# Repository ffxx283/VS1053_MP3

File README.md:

# VS1053_MP3
基于VS1053芯片设计的MP3播放器

产品定位为一款可以对VS1053进行全面开发的开发板，产品的功能应当全面覆盖芯片的所有外设资源，但应该以将VS1053作为主控为重点，适当开发从机功能（SPI控制）。
TYPE-C接口，插入电脑直接对开发板进行下载调试（板载下载器），将读写SD卡的功能也加入此接口中（读卡器功能），可以使用跳线帽进行选择USB的通路。
带有液晶显示屏或者是OLED显示屏，带有按键，方便进行交互。

TYPE-C接口，插入电脑直接对开发板进行下载调试（板载下载器），将读写SD卡的功能也加入此接口中（读卡器功能），可以使用跳线帽进行选择USB的通路。

带有液晶显示屏或者是OLED显示屏，带有按键，方便进行交互。

主控：VS1053
USB转串口芯片：CH340N
SPI存储器芯片：AT93C66
电源芯片：RT9193-33GB、RT9193-18GB
SD卡控制器芯片：GL823
模拟单刀双掷开关SGM3157YC6/TR
显示屏选型：鸿欣达----YT144S025不带触摸
存储设备：TF卡
音频输入输出：3.5mm耳机孔输出+板载MIC

……
不测试了，下载调试软件的时候，软件直接就崩溃了，多次测试均未见效果，当成一个读卡器来用吧
VS1053芯片的生态不行，目前市面上大部分都是把它当做一个从机芯片来用，用作主机的案例太少，
官方对于此方面不够重视，软件也存在各种各样的问题，折腾不下去了。

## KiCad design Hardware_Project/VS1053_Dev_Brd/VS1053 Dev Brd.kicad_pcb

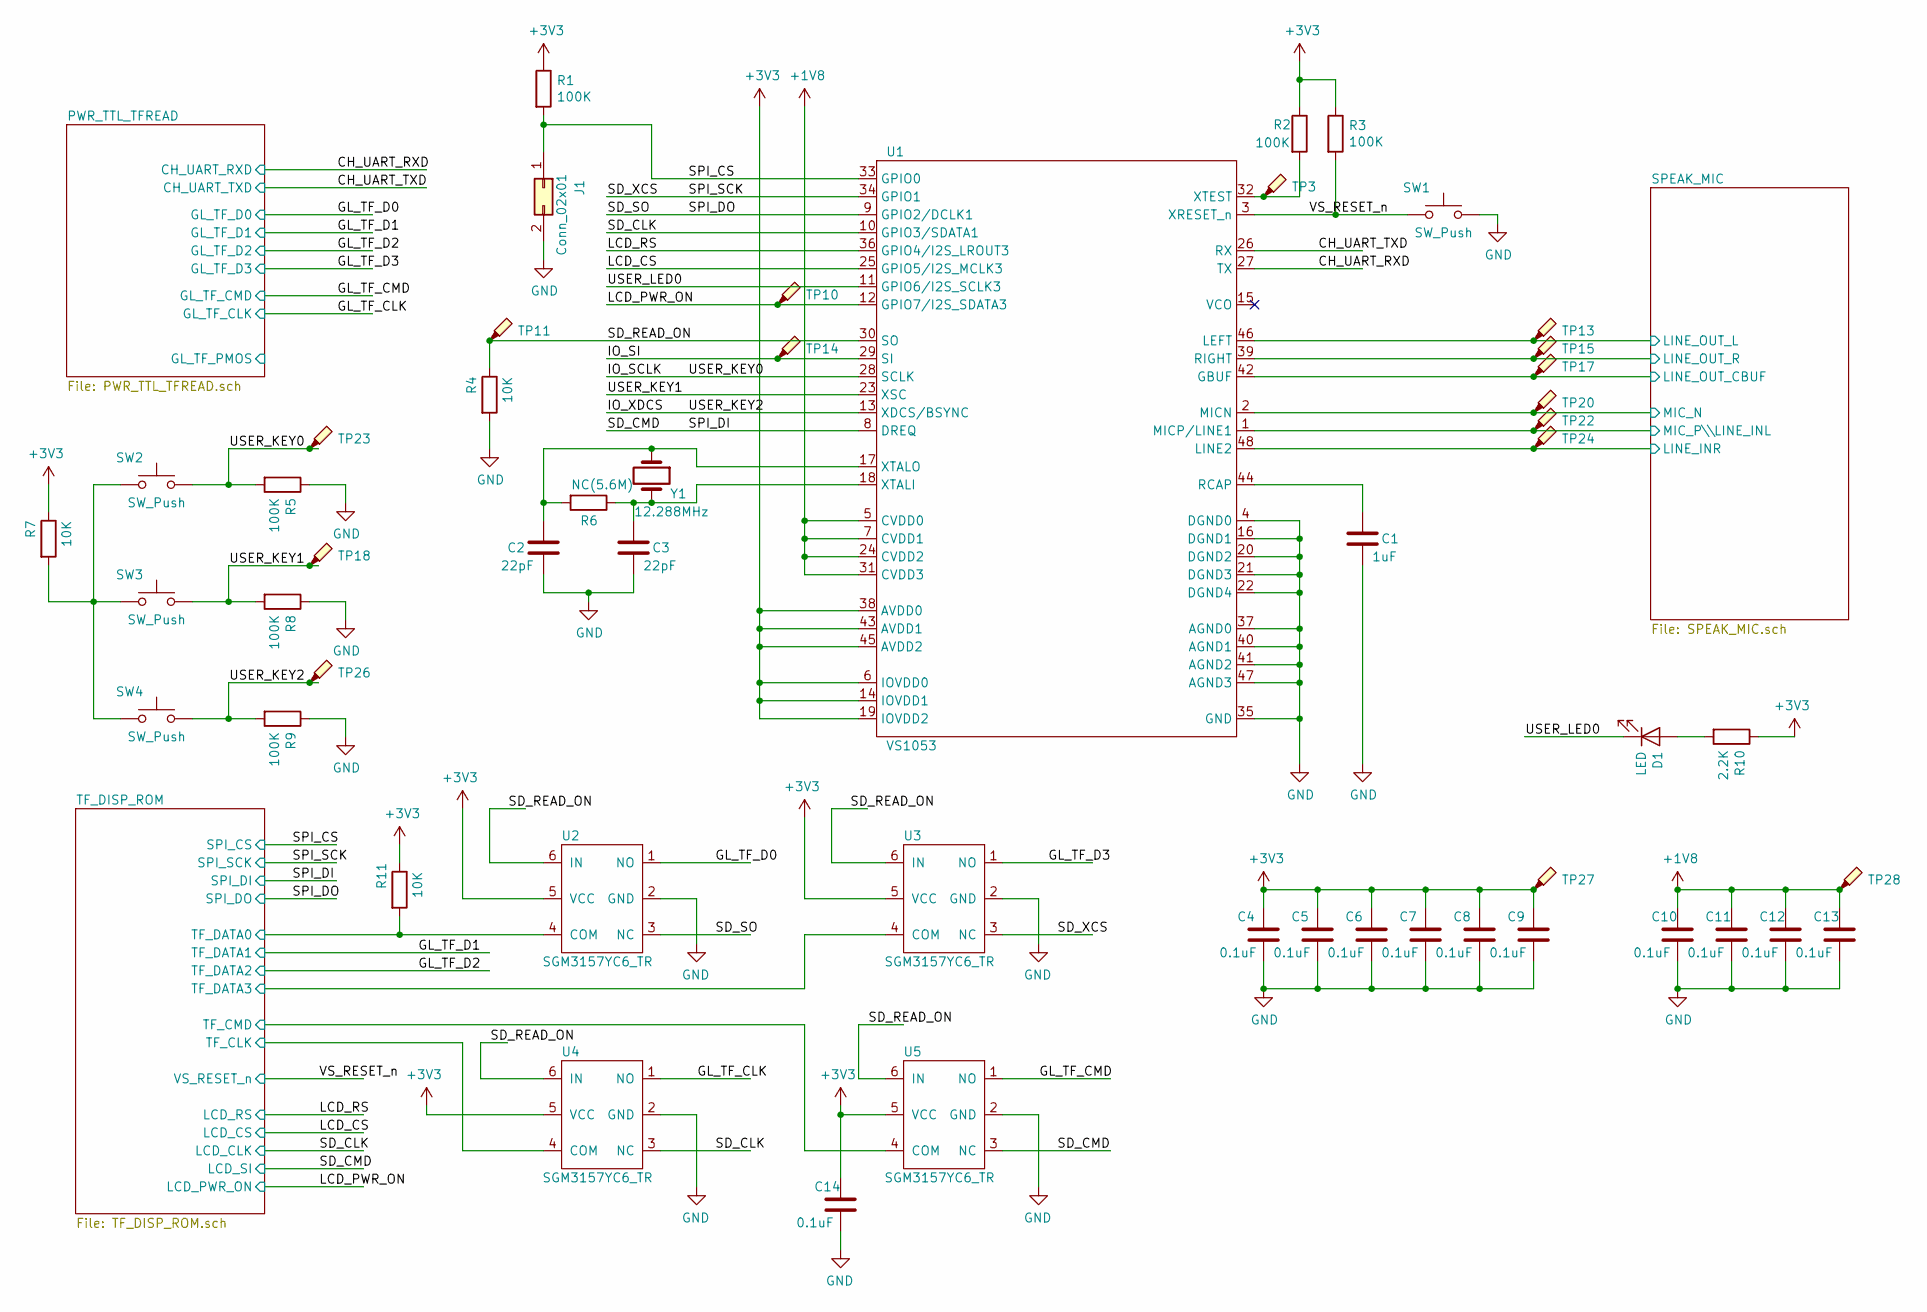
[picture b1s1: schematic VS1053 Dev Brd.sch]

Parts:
C1: 1uF; C_0603_1608Metric
C2, C3: 22pF; C_0402_1005Metric
C4, C5, C6, C7, C8, C9, C10, C11, C12, C13, C14: 0.1uF; C_0402_1005Metric
D1: LED; D_0603_1608Metric
J1: Conn_02x01; PinHeader_1x02_P2.00mm_Vertical
R1, R2, R3, R5, R8, R9: 100K; R_0402_1005Metric
R4, R7, R11: 10K; R_0402_1005Metric
R6: NC(5.6M); R_0402_1005Metric
R10: 2.2K; R_0402_1005Metric
SW1, SW2, SW3, SW4: SW_Push; SW_SPST_B3U-1000P
TP3, TP10, TP11, TP13, TP14, TP15, TP17, TP18, TP20, TP22, TP23, TP24, TP26, TP27, TP28: TestPoint_Probe; TestPoint_Pad_D1.0mm
U1: VS1053; LQFP-48_7x7mm_P0.5mm
U2, U3, U4, U5: SGM3157YC6_TR; SOT-363_SC-70-6
Y1: 12.288MHz; Crystal_HC49-4H_Vertical

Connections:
+1V8: C10.1, C11.1, C12.1, C13.1, TP28.1, U1.5 (CVDD0), U1.7 (CVDD1), U1.24 (CVDD2), U1.31 (CVDD3); also elsewhere on the board
+3V3: C4.1, C5.1, C6.1, C7.1, C8.1, C9.1, C14.1, R1.1, R2.1, R3.1, R7.1, R10.1, R11.1, TP27.1, U1.6 (IOVDD0), U1.14 (IOVDD1), U1.19 (IOVDD2), U1.38 (AVDD0), U1.43 (AVDD1), U1.45 (AVDD2), U2.5 (VCC), U3.5 (VCC), U4.5 (VCC), U5.5 (VCC); also elsewhere on the board
/CH_UART_RXD: U1.27 (TX); also elsewhere on the board
/CH_UART_TXD: U1.26 (RX); also elsewhere on the board
/GL_TF_CLK: U4.1 (NO); also elsewhere on the board
/GL_TF_CMD: U5.1 (NO); also elsewhere on the board
/GL_TF_D0: U2.1 (NO); also elsewhere on the board
/GL_TF_D3: U3.1 (NO); also elsewhere on the board
/IO_SCLK: R5.2, SW2.2, TP23.1, U1.28 (SCLK)
/IO_SI: TP14.1, U1.29 (SI)
/IO_XDCS: R9.2, SW4.2, TP26.1, U1.13 (XDCS/BSYNC)
/LCD_CS: U1.25 (GPIO5/I2S_MCLK3); also elsewhere on the board
/LCD_PWR_ON: TP10.1, U1.12 (GPIO7/I2S_SDATA3); also elsewhere on the board
/LCD_RS: U1.36 (GPIO4/I2S_LROUT3); also elsewhere on the board
/SD_CLK: U1.10 (GPIO3/SDATA1), U4.3 (NC); also elsewhere on the board
/SD_CMD: U1.8 (DREQ), U5.3 (NC); also elsewhere on the board
/SD_READ_ON: R4.1, TP11.1, U1.30 (SO), U2.6 (IN), U3.6 (IN), U4.6 (IN), U5.6 (IN)
/SD_SO: U1.9 (GPIO2/DCLK1), U2.3 (NC); also elsewhere on the board
/SD_XCS: U1.34 (GPIO1), U3.3 (NC); also elsewhere on the board
/SPEAK_MIC/LINE_INR: TP24.1, U1.48 (LINE2); also elsewhere on the board
/SPEAK_MIC/LINE_OUT_CBUF: TP17.1, U1.42 (GBUF); also elsewhere on the board
/SPEAK_MIC/LINE_OUT_L: TP13.1, U1.46 (LEFT); also elsewhere on the board
/SPEAK_MIC/LINE_OUT_R: TP15.1, U1.39 (RIGHT); also elsewhere on the board
/SPEAK_MIC/MIC_N: TP20.1, U1.2 (MICN); also elsewhere on the board
/SPEAK_MIC/MIC_P\LINE_INL: TP22.1, U1.1 (MICP/LINE1); also elsewhere on the board
/SPI_CS: J1.1, R1.2, U1.33 (GPIO0); also elsewhere on the board
/TF_DISP_ROM/TF_CLK: U4.4 (COM); also elsewhere on the board
/TF_DISP_ROM/TF_CMD: U5.4 (COM); also elsewhere on the board
/TF_DISP_ROM/TF_DATA0: R11.2, U2.4 (COM); also elsewhere on the board
/TF_DISP_ROM/TF_DATA3: U3.4 (COM); also elsewhere on the board
/USER_KEY1: R8.2, SW3.2, TP18.1, U1.23 (XSC)
/USER_LED0: D1.1 (K), U1.11 (GPIO6/I2S_SCLK3)
/VS_RESET_n: R3.2, SW1.1, U1.3 (XRESET_n); also elsewhere on the board
GND: C1.2, C2.1, C3.2, C4.2, C5.2, C6.2, C7.2, C8.2, C9.2, C10.2, C11.2, C12.2, C13.2, C14.2, J1.2, R4.2, R5.1, R8.1, R9.1, SW1.2, U1.4 (DGND0), U1.16 (DGND1), U1.20 (DGND2), U1.21 (DGND3), U1.22 (DGND4), U1.35 (GND), U1.37 (AGND0), U1.40 (AGND1), U1.41 (AGND2), U1.47 (AGND3), U2.2 (GND), U3.2 (GND), U4.2 (GND), U5.2 (GND); also elsewhere on the board
unnamed: C1.1, U1.44 (RCAP)
unnamed: C2.2, R6.2, U1.17 (XTALO), Y1.1
unnamed: C3.1, R6.1, U1.18 (XTALI), Y1.2
unnamed: D1.2 (A), R10.2
unnamed: R2.2, TP3.1, U1.32 (XTEST)
unnamed: R7.2, SW2.1, SW3.1, SW4.1

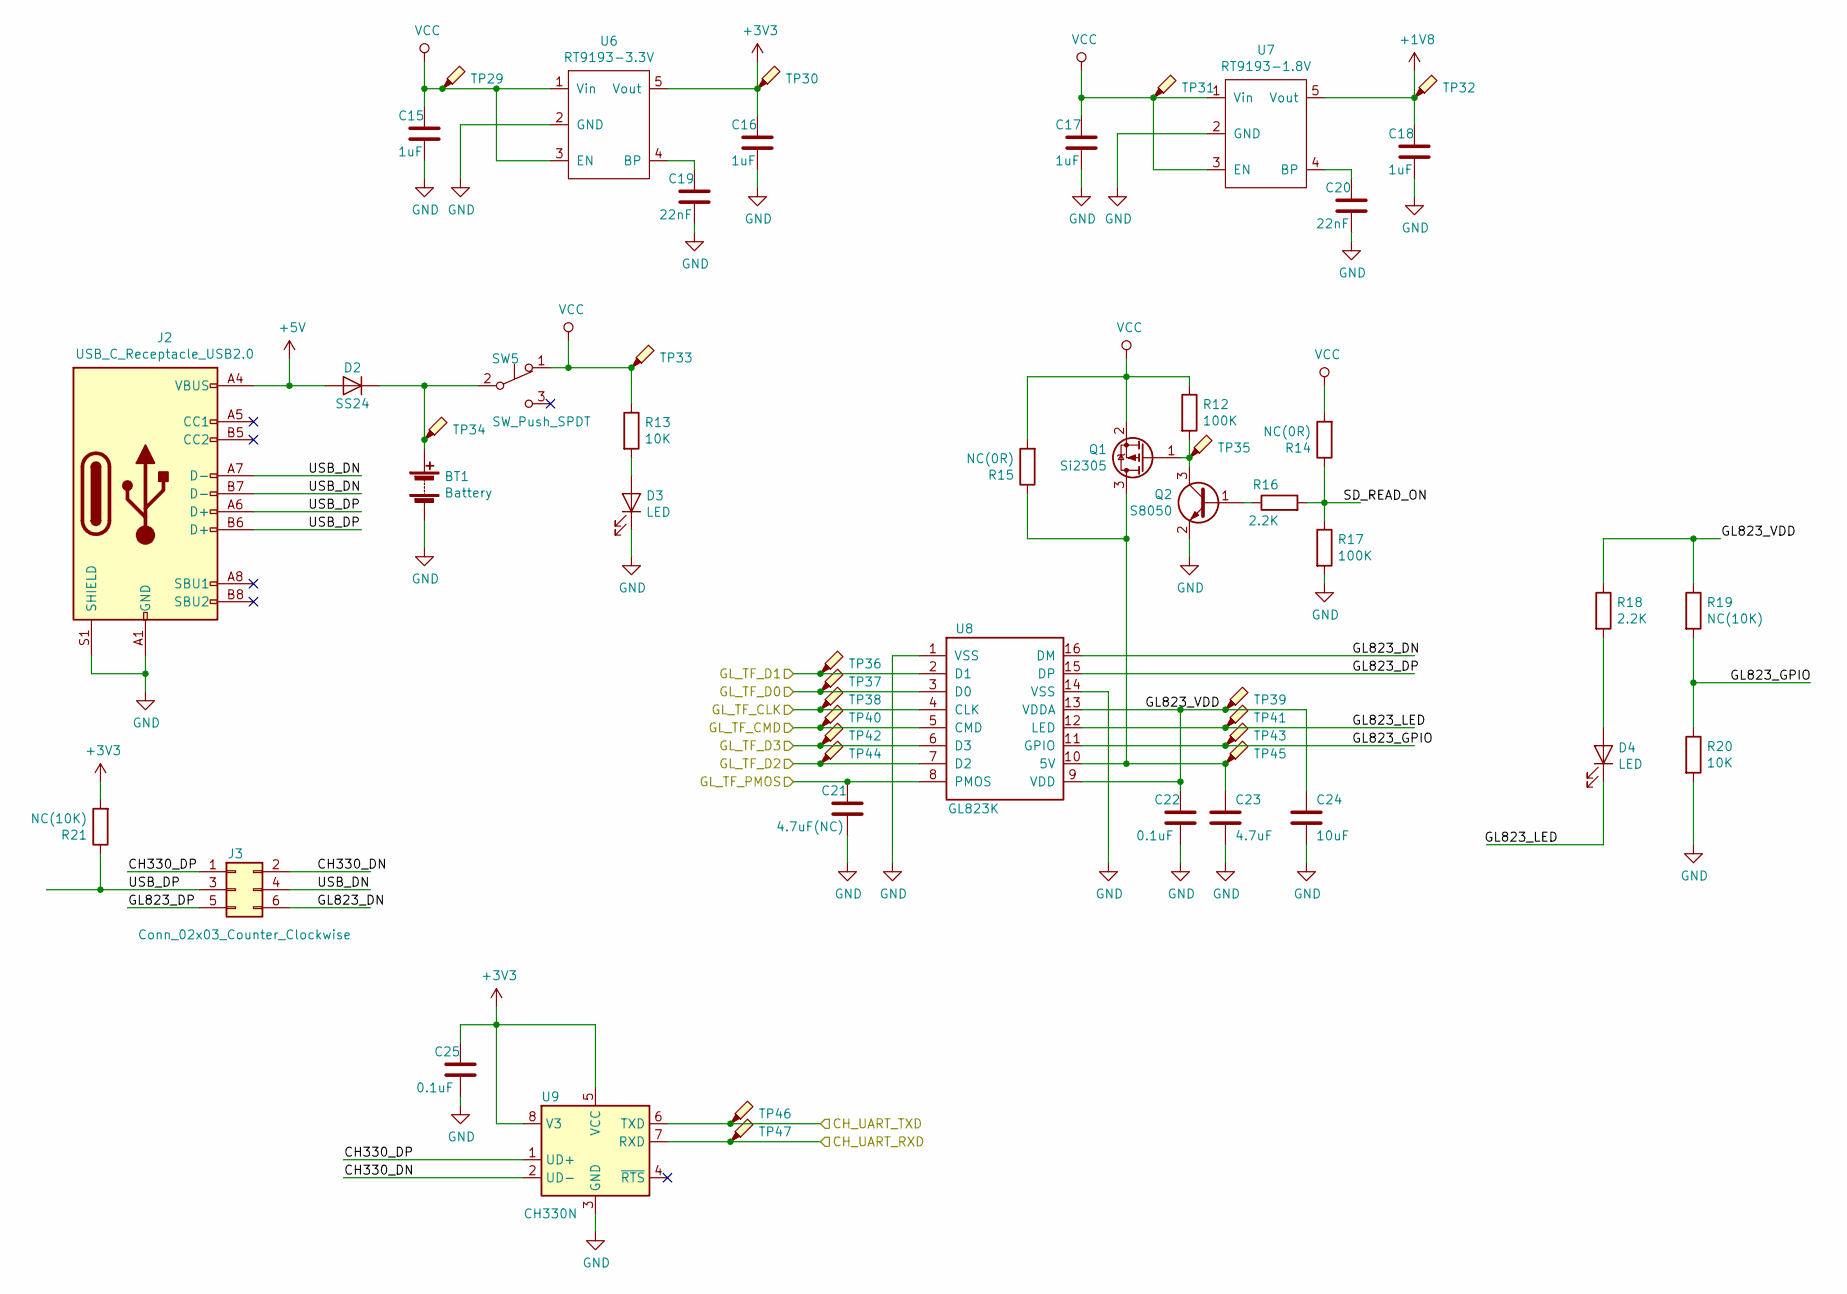
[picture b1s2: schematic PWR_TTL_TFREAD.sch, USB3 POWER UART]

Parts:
BT1: Battery; PinHeader_1x02_P2.54mm_Vertical
C15, C16, C17, C18: 1uF; C_0603_1608Metric
C19, C20: 22nF; C_0402_1005Metric
C21: 4.7uF(NC); C_0603_1608Metric
C22, C25: 0.1uF; C_0402_1005Metric
C23: 4.7uF; C_0603_1608Metric
C24: 10uF; C_0603_1608Metric
D2: SS24; D_SMA
D3, D4: LED; D_0603_1608Metric
J2: USB_C_Receptacle_USB2.0; USB_C_Receptacle_Palconn_UTC16-G
J3: Conn_02x03_Counter_Clockwise; PinHeader_2x03_P2.00mm_Vertical
Q1: Si2305; SOT-23
Q2: S8050; SOT-23
R12, R17: 100K; R_0402_1005Metric
R13, R20: 10K; R_0402_1005Metric
R14, R15: NC(0R); R_0402_1005Metric
R16, R18: 2.2K; R_0402_1005Metric
R19, R21: NC(10K); R_0402_1005Metric
SW5: SW_Push_SPDT; SW_CuK_OS102011MA1QN1_SPDT_Angled
TP29, TP30, TP31, TP32, TP33, TP34, TP35, TP36, TP37, TP38, TP39, TP40, TP41, TP42, TP43, TP44, TP45, TP46, TP47: TestPoint_Probe; TestPoint_Pad_D1.0mm
U6: RT9193-3.3V; SOT-353_SC-70-5
U7: RT9193-1.8V; SOT-353_SC-70-5
U8: GL823K; SSOP-16_5.3x6.2mm_P0.65mm
U9: CH330N; SOIC-8_3.9x4.9mm_P1.27mm

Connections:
+1V8: C18.1, TP32.1, U7.5 (Vout); also elsewhere on the board
+3V3: C16.1, C25.1, R21.2, TP30.1, U6.5 (Vout), U9.5 (VCC), U9.8 (V3); also elsewhere on the board
+5V: D2.2 (A), J2.A4 (VBUS), J2.A9 (VBUS), J2.B4 (VBUS), J2.B9 (VBUS)
/CH_UART_RXD: TP47.1, U9.7 (RXD); also elsewhere on the board
/CH_UART_TXD: TP46.1, U9.6 (TXD); also elsewhere on the board
/GL_TF_CLK: TP38.1, U8.4 (CLK); also elsewhere on the board
/GL_TF_CMD: TP40.1, U8.5 (CMD); also elsewhere on the board
/GL_TF_D0: TP37.1, U8.3 (D0); also elsewhere on the board
/GL_TF_D1: TP36.1, U8.2 (D1); also elsewhere on the board
/GL_TF_D2: TP44.1, U8.7 (D2); also elsewhere on the board
/GL_TF_D3: TP42.1, U8.6 (D3); also elsewhere on the board
/PWR_TTL_TFREAD/CH330_DN: J3.2 (Pin_6), U9.2 (UD-)
/PWR_TTL_TFREAD/CH330_DP: J3.1, U9.1 (UD+)
/PWR_TTL_TFREAD/GL823_DN: J3.6 (Pin_4), U8.16 (DM)
/PWR_TTL_TFREAD/GL823_DP: J3.5 (Pin_3), U8.15 (DP)
/PWR_TTL_TFREAD/GL823_GPIO: R19.2, R20.1, TP43.1, U8.11 (GPIO)
/PWR_TTL_TFREAD/GL823_LED: D4.1 (K), TP41.1, U8.12 (LED)
/PWR_TTL_TFREAD/GL823_VDD: C22.1, C24.1, R18.1, R19.1, TP39.1, U8.9 (VDD), U8.13 (VDDA)
/PWR_TTL_TFREAD/GL_TF_PMOS: C21.1, U8.8 (PMOS)
/PWR_TTL_TFREAD/SD_READ_ON: R14.1, R16.2, R17.1
/PWR_TTL_TFREAD/USB_DN: J2.A7 (D-), J2.B7 (D-), J3.4 (Pin_5)
/PWR_TTL_TFREAD/USB_DP: J2.A6 (D+), J2.B6 (D+), J3.3 (Pin_2), R21.1
GND: BT1.2 (-), C15.2, C16.2, C17.2, C18.2, C19.2, C20.2, C21.2, C22.2, C23.2, C24.2, C25.2, D3.1 (K), J2.A1 (GND), J2.A12 (GND), J2.B1 (GND), J2.B12 (GND), J2.S1 (SHIELD), Q2.2 (E), R17.2, R20.2, U6.2 (GND), U7.2 (GND), U8.1 (VSS), U8.14 (VSS), U9.3 (GND); also elsewhere on the board
unnamed: BT1.1 (+), D2.1 (K), SW5.2 (B), TP34.1
unnamed: C19.1, U6.4 (BP)
unnamed: C20.1, U7.4 (BP)
unnamed: C23.1, Q1.3 (D), R15.1, TP45.1, U8.10 (5V)
unnamed: D3.2 (A), R13.2
unnamed: D4.2 (A), R18.2
unnamed: Q1.1 (G), Q2.3 (C), R12.2, TP35.1
unnamed: Q2.1 (B), R16.1
VCC: C15.1, C17.1, Q1.2 (S), R12.1, R13.1, R14.2, R15.2, SW5.1 (A), TP29.1, TP31.1, TP33.1, U6.1 (Vin), U6.3 (EN), U7.1 (Vin), U7.3 (EN); also elsewhere on the board

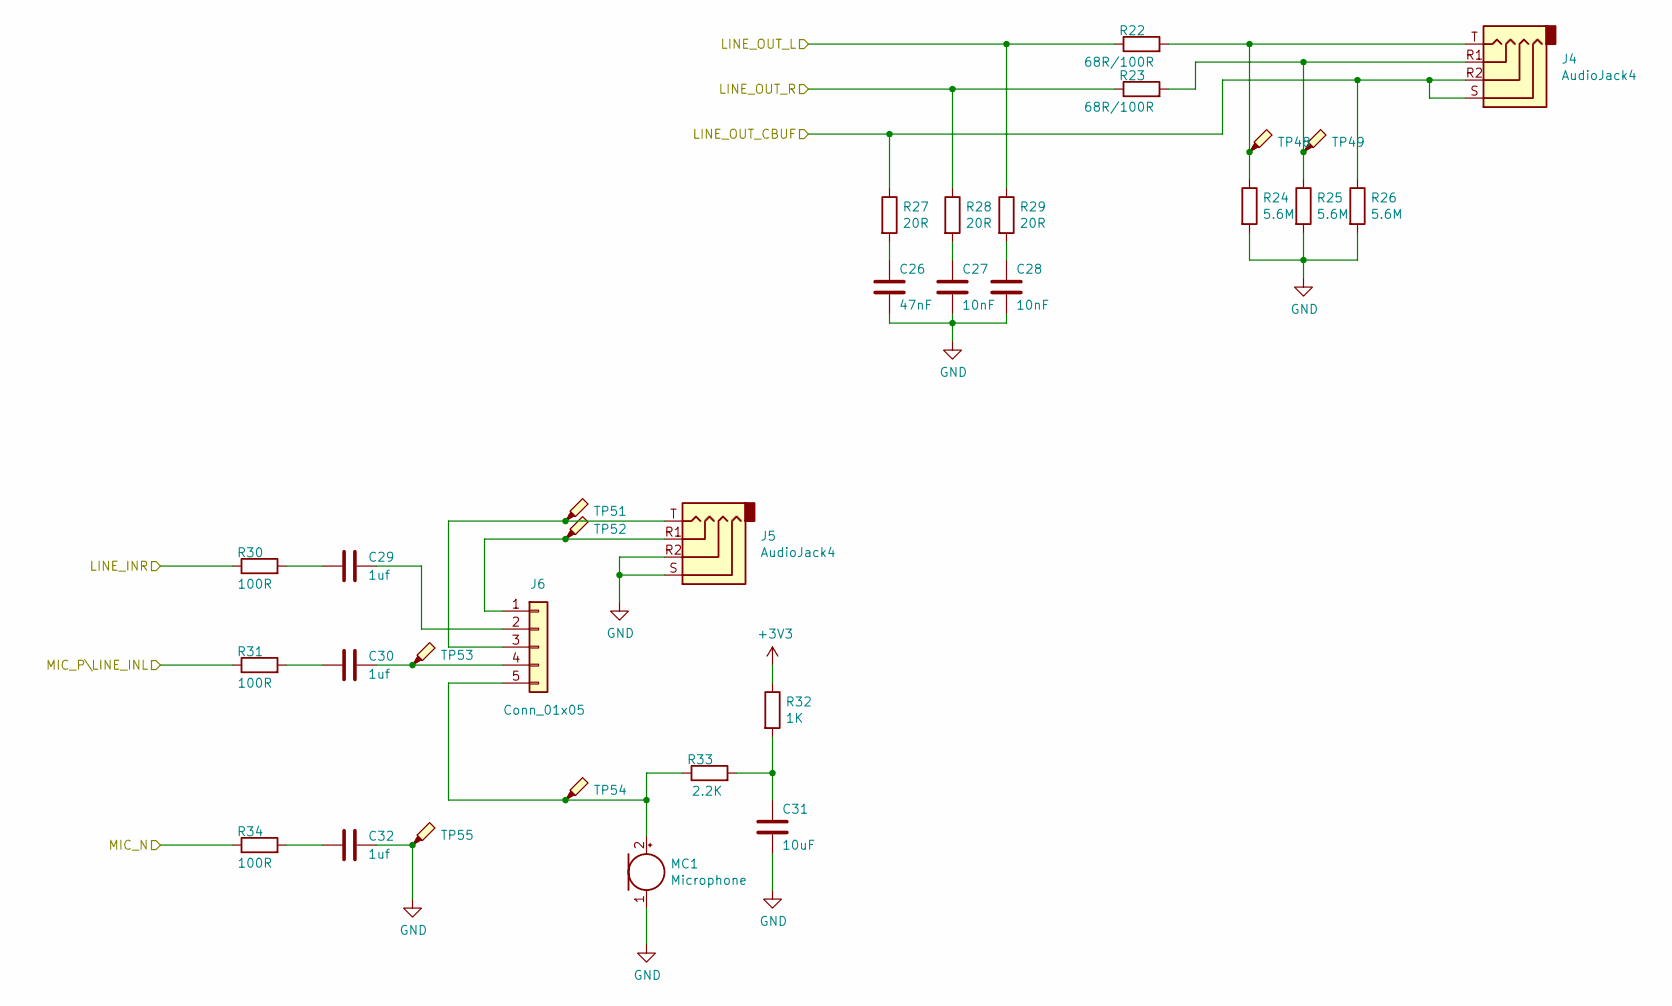
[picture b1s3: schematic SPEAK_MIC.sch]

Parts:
C26: 47nF; C_0603_1608Metric
C27, C28: 10nF; C_0402_1005Metric
C29, C30, C32: 1uf; C_0603_1608Metric
C31: 10uF; C_0603_1608Metric
J4, J5: AudioJack4; Jack_3.5mm_PJ320D_Horizontal
J6: Conn_01x05; PinHeader_1x05_P2.00mm_Vertical
MC1: Microphone; PinHeader_1x02_P2.00mm_Vertical
R22, R23: 68R/100R; R_0402_1005Metric
R24, R25, R26: 5.6M; R_0402_1005Metric
R27, R28, R29: 20R; R_0402_1005Metric
R30, R31, R34: 100R; R_0402_1005Metric
R32: 1K; R_0402_1005Metric
R33: 2.2K; R_0402_1005Metric
TP48, TP49, TP51, TP52, TP53, TP54, TP55: TestPoint_Probe; TestPoint_Pad_D1.0mm

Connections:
+3V3: R32.1; also elsewhere on the board
/SPEAK_MIC/LINE_INR: R30.1; also elsewhere on the board
/SPEAK_MIC/LINE_OUT_CBUF: J4.R2, J4.S, R26.1, R27.1; also elsewhere on the board
/SPEAK_MIC/LINE_OUT_L: R22.1, R29.1; also elsewhere on the board
/SPEAK_MIC/LINE_OUT_R: R23.1, R28.1; also elsewhere on the board
/SPEAK_MIC/MIC_N: R34.1; also elsewhere on the board
/SPEAK_MIC/MIC_P\LINE_INL: R31.1; also elsewhere on the board
GND: C26.2, C27.2, C28.2, C31.2, C32.2, J5.R2, J5.S, MC1.1 (-), R24.2, R25.2, R26.2, TP55.1; also elsewhere on the board
unnamed: C26.1, R27.2
unnamed: C27.1, R28.2
unnamed: C28.1, R29.2
unnamed: C29.1, R30.2
unnamed: C29.2, J6.2
unnamed: C30.1, R31.2
unnamed: C30.2, J6.4, TP53.1
unnamed: C31.1, R32.2, R33.2
unnamed: C32.1, R34.2
unnamed: J4.R1, R23.2, R25.1, TP49.1
unnamed: J4.T, R22.2, R24.1, TP48.1
unnamed: J5.R1, J6.1, TP52.1
unnamed: J5.T, J6.3, TP51.1
unnamed: J6.5, MC1.2 (+), R33.1, TP54.1

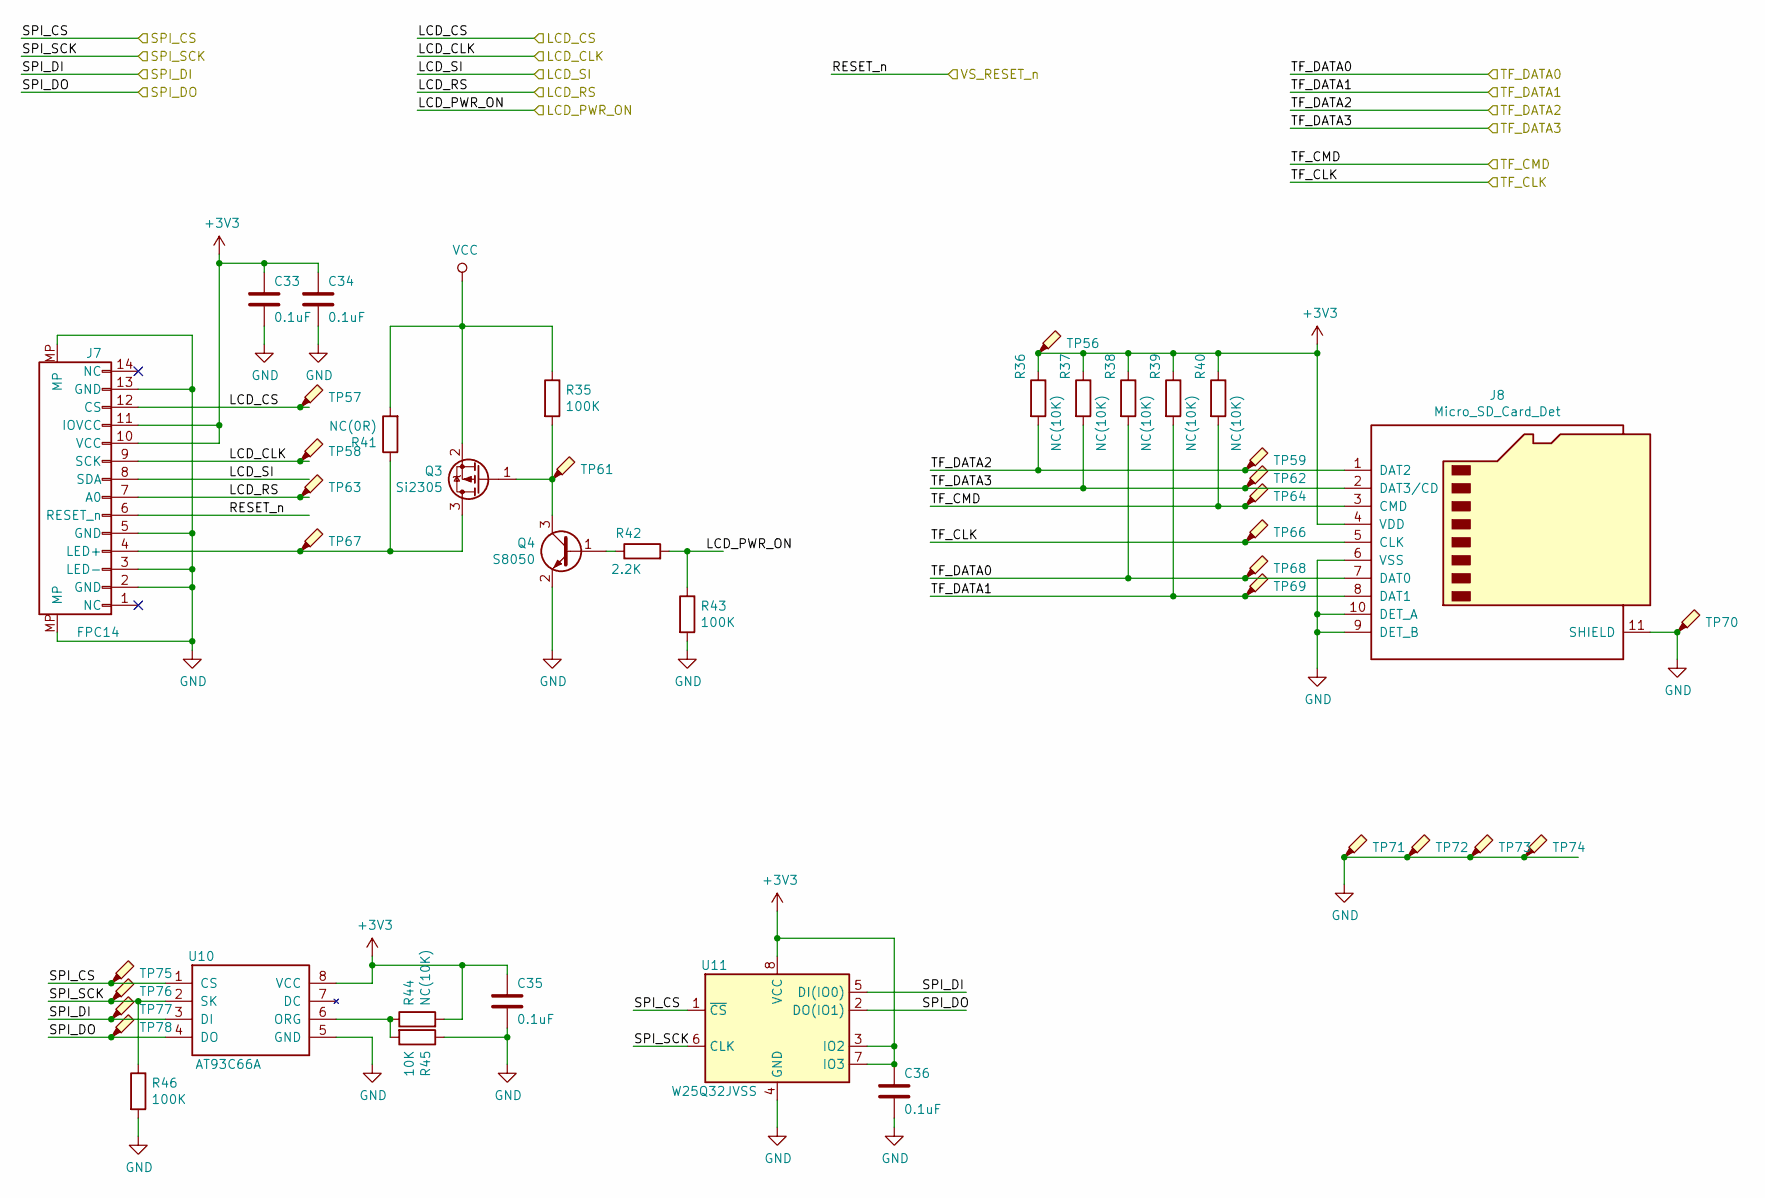
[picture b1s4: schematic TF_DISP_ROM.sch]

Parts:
C33, C34, C35, C36: 0.1uF; C_0402_1005Metric
J7: FPC14; TE_1-1734839-4_1x14-1MP_P0.5mm_Horizontal
J8: Micro_SD_Card_Det; SD-MINI-X
Q3: Si2305; SOT-23
Q4: S8050; SOT-23
R35, R43, R46: 100K; R_0402_1005Metric
R36, R37, R38, R39, R40, R44: NC(10K); R_0402_1005Metric
R41: NC(0R); R_0402_1005Metric
R42: 2.2K; R_0402_1005Metric
R45: 10K; R_0402_1005Metric
TP56, TP57, TP58, TP59, TP61, TP62, TP63, TP64, TP66, TP67, TP68, TP69, TP70, TP71, TP72, TP73, TP74, TP75, TP76, TP77, TP78: TestPoint_Probe; TestPoint_Pad_D1.0mm
U10: AT93C66A; SOIC-8_5.275x5.275mm_P1.27mm
U11: W25Q32JVSS; SOIC-8_5.275x5.275mm_P1.27mm

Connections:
+3V3: C33.1, C34.1, C35.1, C36.1, J7.10 (VCC), J7.11 (IOVCC), J8.4 (VDD), R36.1, R37.1, R38.1, R39.1, R40.1, R44.2, TP56.1, U10.8 (VCC), U11.3 (IO2), U11.7 (IO3), U11.8 (VCC); also elsewhere on the board
/GL_TF_D1: J8.8 (DAT1), R39.2, TP69.1; also elsewhere on the board
/GL_TF_D2: J8.1 (DAT2), R36.2, TP59.1; also elsewhere on the board
/LCD_CS: J7.12 (CS), TP57.1; also elsewhere on the board
/LCD_PWR_ON: R42.2, R43.1; also elsewhere on the board
/LCD_RS: J7.7 (A0), TP63.1; also elsewhere on the board
/SD_CLK: J7.9 (SCK), TP58.1; also elsewhere on the board
/SD_CMD: J7.8 (SDA), TP77.1, U10.3 (DI), U11.5 (DI(IO0)); also elsewhere on the board
/SD_SO: TP78.1, U10.4 (DO), U11.2 (DO(IO1)); also elsewhere on the board
/SD_XCS: R46.1, TP76.1, U10.2 (SK), U11.6 (CLK); also elsewhere on the board
/SPI_CS: TP75.1, U10.1 (CS), U11.1 (~CS); also elsewhere on the board
/TF_DISP_ROM/TF_CLK: J8.5 (CLK), TP66.1; also elsewhere on the board
/TF_DISP_ROM/TF_CMD: J8.3 (CMD), R40.2, TP64.1; also elsewhere on the board
/TF_DISP_ROM/TF_DATA0: J8.7 (DAT0), R38.2, TP68.1; also elsewhere on the board
/TF_DISP_ROM/TF_DATA3: J8.2 (DAT3/CD), R37.2, TP62.1; also elsewhere on the board
/VS_RESET_n: J7.6 (RESET_n); also elsewhere on the board
GND: C33.2, C34.2, C35.2, C36.2, J7.2 (GND), J7.3 (LED-), J7.5 (GND), J7.13 (GND), J7.MP, J8.6 (VSS), J8.9 (DET_B), J8.10 (DET_A), J8.11 (SHIELD), Q4.2 (E), R43.2, R45.1, R46.2, TP70.1, TP71.1, TP72.1, TP73.1, TP74.1, U10.5 (GND), U11.4 (GND); also elsewhere on the board
unnamed: J7.4 (LED+), Q3.3 (D), R41.1, TP67.1
unnamed: Q3.1 (G), Q4.3 (C), R35.2, TP61.1
unnamed: Q4.1 (B), R42.1
unnamed: R44.1, R45.2, U10.6 (ORG)
VCC: Q3.2 (S), R35.1, R41.2; also elsewhere on the board

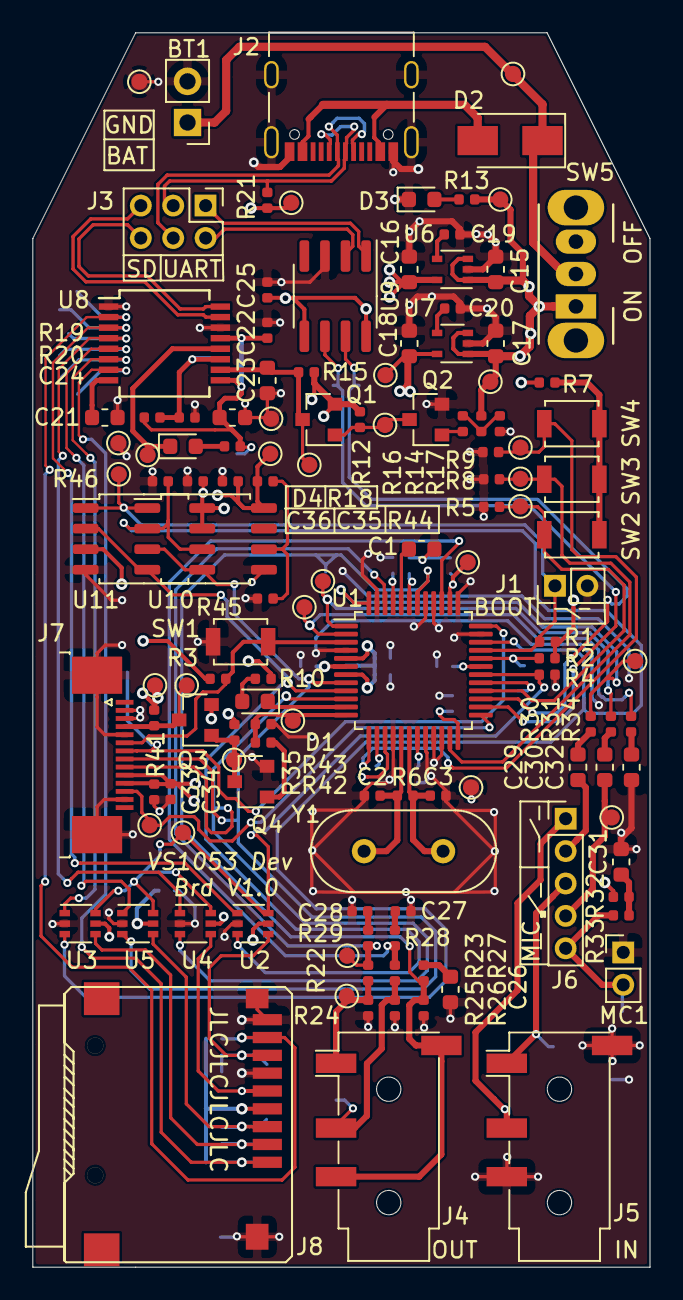
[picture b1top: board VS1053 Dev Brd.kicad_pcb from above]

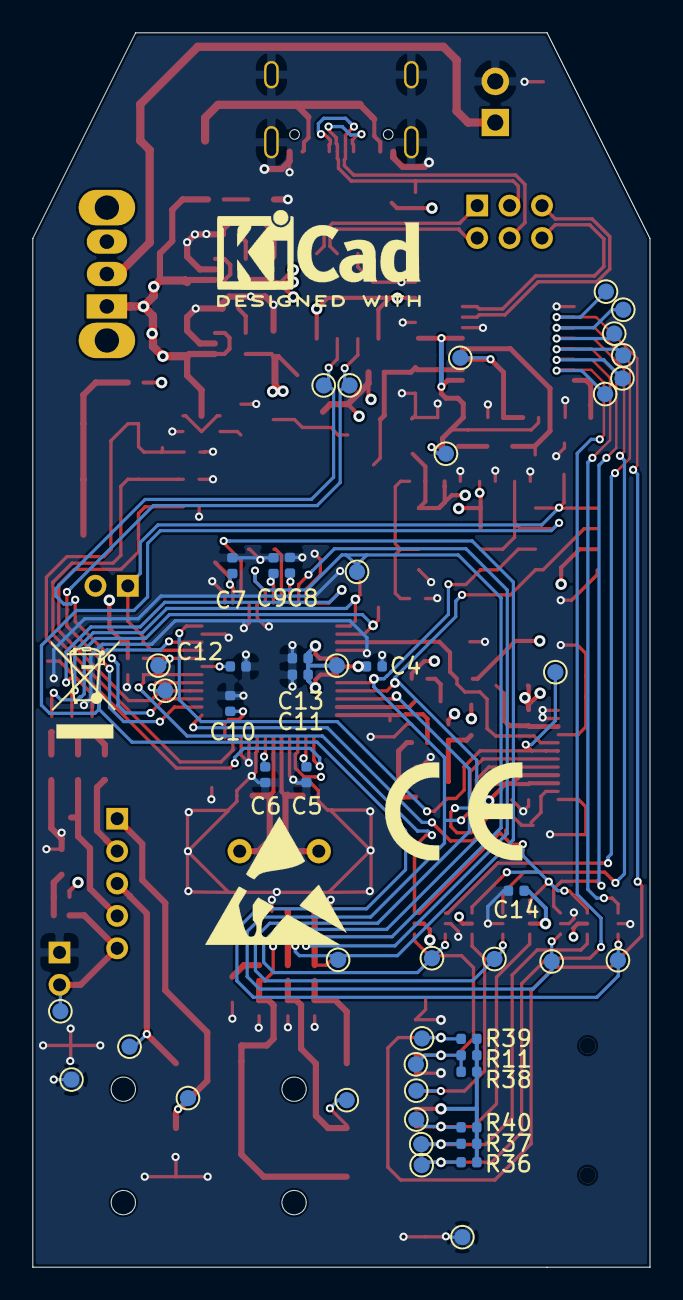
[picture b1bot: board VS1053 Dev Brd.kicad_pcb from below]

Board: 4 copper layers, 38.1 x 76.2 mm, 179 parts (49 on the bottom side), 81 nets.

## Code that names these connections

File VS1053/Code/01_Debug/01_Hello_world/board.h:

#ifndef __BOARD_H__
#define __BOARD_H__

#include <gpio.h>


// some hardware-specific defines for VS1053 prototyping boards.
//
// define ONE of the following before including this file
// ~~~~~~~~~~~~~~~~~~~~~~~~~~~~~~~~
//
// USE_PROTOTYPING_BOARD -- VS10XX prototyping board
// USE_SIMPLE_DSP_BOARD -- "simple DSP" with host board


//
// --------- DEFINITIONS FOR VS1053 SIMPLE DSP BOARD ------------
//
#ifdef USE_SIMPLE_DSP_BOARD

#define BUTTON_1 (1 << 3) /* Button 1 is at GPIO3 */
#define BUTTON_1_PRESSED GPIO_IS_HIGH(BUTTON_1)
#define CONFIGURE_BUTTON_1 {GPIO_CONFIGURE_AS_INPUT(BUTTON_1);}

#define LED_1 (1 << 4) /* Led 1 is at GPIO4 */
#define LED_2 (1 << 5) /* Led 2 is at GPIO5 */
#define LED_3 (1 << 6) /* Led 3 is at GPIO6 */
#define LED_4 (1 << 7) /* Led 4 is at GPIO7 */

#define SET_LED_1_ON GPIO_SET_HIGH(LED_1)
#define SET_LED_1_OFF GPIO_SET_LOW(LED_1)
#define SET_LED_2_ON GPIO_SET_HIGH(LED_2)
#define SET_LED_2_OFF GPIO_SET_LOW(LED_2)
#define SET_LED_3_ON GPIO_SET_HIGH(LED_3)
#define SET_LED_3_OFF GPIO_SET_LOW(LED_3)
#define SET_LED_4_ON GPIO_SET_HIGH(LED_4)
#define SET_LED_4_OFF GPIO_SET_LOW(LED_4)

#define CONFIGURE_LED_1 {GPIO_CONFIGURE_AS_OUTPUT(LED_1);}
#define CONFIGURE_LED_2 {GPIO_CONFIGURE_AS_OUTPUT(LED_2);}
#define CONFIGURE_LED_3 {GPIO_CONFIGURE_AS_OUTPUT(LED_3);}
#define CONFIGURE_LED_4 {GPIO_CONFIGURE_AS_OUTPUT(LED_4);}
#define CONFIGURE_LEDS {GPIO_CONFUGURE_AS_OUTPUT(LED_1 | LED_2 | LED_3 | LED_4);}

#endif // USE_SIMPLE_DSP


//
// --------- DEFINITIONS FOR VS1053 PROTOTYPING BOARD ------------
//
#ifdef USE_PROTOTYPING_BOARD

// For historical reasons (same PCB is also used for VS1011 and VS1003), the button
// connections in the prototyping board need to be read in a special way:
#define XDCS_PIN (1 << 11) /* button 1 is at xDCS pin */
#define SI_PIN (1 << 10) /* button 2 is at SI pin and via diode D4 also in xDCS pin */
// (button 3 is more difficult to read in the prototyping board, see schematic.)
#define LED_3 (1 << 6) /* Led 3 is at GPIO6 */
#define SET_LED_3_ON GPIO_SET_HIGH(LED_3)
#define SET_LED_3_OFF GPIO_SET_LOW(LED_3)
#define CONFIGURE_LED_3 {GPIO_CONFIGURE_AS_OUTPUT(LED_3);}

#define BUTTON_1_PRESSED ((GPIO_IS_LOW(XDCS_PIN)) && (GPIO_IS_HIGH(SI_PIN)))
#define BUTTON_2_PRESSED (GPIO_IS_LOW(SI_PIN))
#define CONFIGURE_BUTTON_1 {} // No need for configuration, xDCS pin is always input
#define CONFIGURE_BUTTON_2 {} // No need for configuration, xDCS and SI pins are always input

// led 1 is at DREQ pin and DREQ pin is special
#define SET_LED_1_ON DREQ_SET_HIGH
#define SET_LED_1_OFF DREQ_SET_LOW

#define CONFIGURE_LED_1 {} // No need for configuration, DREQ pin is always output
#define CONFIGURE_LEDS {} // No need for configuration, DREQ pin is always output

#endif // USE_PROTOTYPING_BOARD



#endif // __BOARD_H__

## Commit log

2022-12-01 First update
